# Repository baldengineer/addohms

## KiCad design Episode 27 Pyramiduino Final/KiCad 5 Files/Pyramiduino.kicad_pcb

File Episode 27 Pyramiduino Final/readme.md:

For more information on this video, visit https://addohms.squarespace.com/diy-arduino-turn-on.

The "Arduino Code" directory has the "exercise.ino" showed near the end.
"KiCad 5 Files" include the final schematic and PCB files for the series

-James
The Bald Engineer

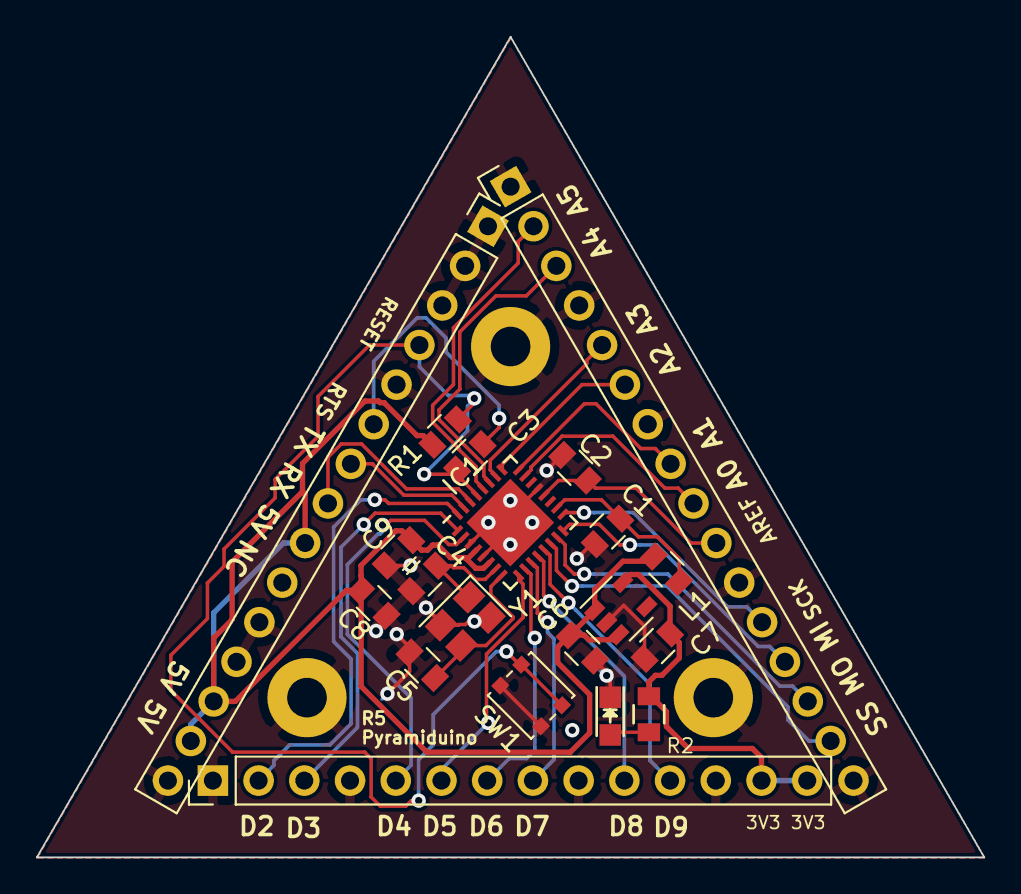
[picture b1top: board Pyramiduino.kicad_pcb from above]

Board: 2 copper layers, 52.6 x 45.6 mm, 23 parts (0 on the bottom side), 30 nets.

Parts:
C1, C3, C9: 100nF; C_0805
C2: 10nF; C_0805
C4, C5: 22pF; C_0805
C6, C7, C8: 1uF; C_0805
D1: LED; LED_0805
IC1: ATMEGA328-A; QFN-32-1EP_5x5mm_Pitch0.5mm-GND
L1: 10uH; C_0805
P1: CONN_01X16; Pin_Header_Straight_1x16_Pitch2.54mm
P2: CONN_01X14; Pin_Header_Straight_1x15_Pitch2.54mm
P3: CONN_01X14; Pin_Header_Straight_1x14_Pitch2.54mm
P4, P5, P6: CONN_01X01; MountingHole_2.2mm_M2_Pad
R1: 100K; C_0805
R2: 1k; C_0805
SW1: SW_PUSH; SW_SPST_PTS830
U1: 3v3; SOT-23-5
Y1: 16M; FA238-4pin_3.2x2.5mm_Offset

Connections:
+3V3: C7.2, P3.13, P3.14, R2.1, U1.5
/328-RX: IC1.30, P2.8
/328-TX: IC1.31, P2.7
/A0: IC1.23, P1.9
/A1: IC1.24, P1.8
/A2: IC1.25, P1.6
/A3: IC1.26, P1.5
/A4: IC1.27, P1.3
/A5: IC1.28, P1.2
/AREF: C2.1, IC1.20, P1.10
/D2: IC1.32, P3.2
/D3: IC1.1, P3.3
/D4: IC1.2, P3.5
/D5: IC1.9, P3.6
/D6: IC1.10, P3.7
/D7: IC1.11, P3.8
/D8: IC1.12, P3.10
/D9: IC1.13, P3.11
/MISO: IC1.16, P1.13
/MOSI: IC1.15, P1.14
/RESET: C3.1, IC1.29, P2.4, R1.2, SW1.2
/RTS: C3.2, P2.6
/SCK: IC1.17, P1.12
/SS: IC1.14, P1.15
/X_N: C5.2, IC1.8, Y1.3
/X_P: C4.2, IC1.7, Y1.1
GND: C1.2, C2.2, C4.1, C5.1, C6.1, C7.1, C8.2, C9.2, D1.1, IC1.3, IC1.5, IC1.21, P1.1, P1.4, P1.7, P1.11, P1.16, P2.1, P2.2, P2.3, P2.5, P2.11, P2.12, P2.15, P3.1, P3.4, P3.9, P3.12, P4.1, P5.1, P6.1, SW1.1, U1.2, Y1.2, Y1.4
unnamed: C1.1, IC1.18, L1.1
unnamed: D1.2, R2.2
VCC: C6.2, C8.1, C9.1, IC1.4, IC1.6, L1.2, P2.9, P2.13, P2.14, R1.1, U1.1, U1.3

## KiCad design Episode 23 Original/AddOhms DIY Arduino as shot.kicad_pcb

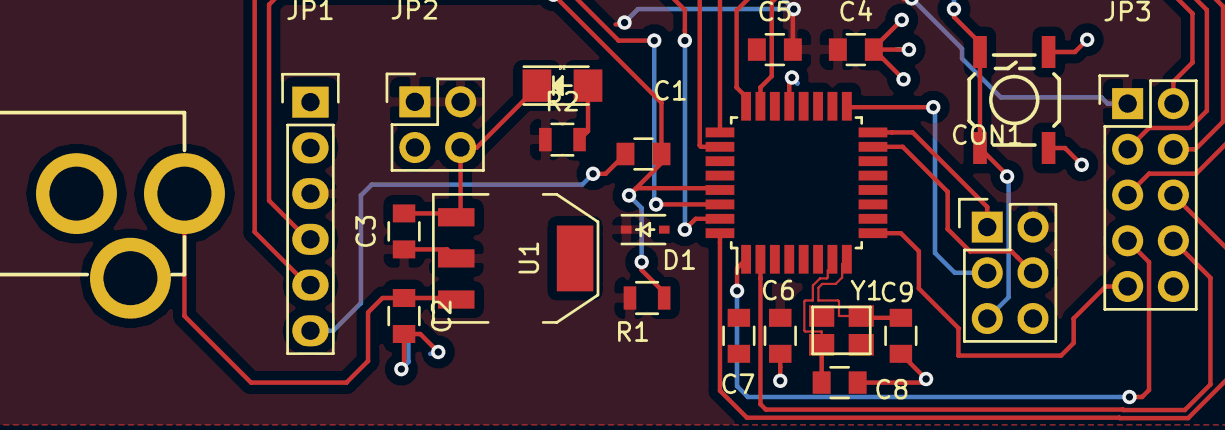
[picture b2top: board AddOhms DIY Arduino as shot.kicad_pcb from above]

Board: 2 copper layers, 22 parts (0 on the bottom side), 21 nets.

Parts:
C1, C4, C5, C6, C7: 100nF; C_0805
C2: 10uF; C_0805
C3: 1uF; C_0805
C8, C9: 22pF; C_0805
CON1: AVR-ISP-6; Pin_Header_Straight_2x03
D1: D; SOD-323
D2: PWR; LED-1206
J1: VIN; POWER_JACK_PTH
JP1: M06; Pin_Header_Straight_1x06
JP2: 5V_HDR; Pin_Header_Straight_2x02
JP3: M10; Pin_Header_Straight_2x05
R1: R; R_0805
R2: 1K; R_0805
SW1: RESET; SW_PUSHBUTTON_SMD
U1: NCP1117-12_TO252; SOT-223
U2: ATMEGA168A-AU; TQFP-32_7x7mm_Pitch0.8mm
Y1: Crystal; crystal_FA238-TSX3225

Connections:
+5V: C3.1, C4.1, C5.1, C6.1, C7.1, CON1.2, D1.1, JP1.3, JP2.1, JP2.2, JP3.1, R1.1, R2.1, U1.2, U2.4, U2.6, U2.18, U2.20
/328_RX: JP1.4, U2.30
/328_TX: JP1.5, U2.31
/A0: JP3.2, U2.23
/A1: JP3.3, U2.24
/A2: JP3.4, U2.25
/A3: JP3.5, U2.26
/D2: JP3.6, U2.32
/D3: JP3.7, U2.1
/D4: JP3.8, U2.2
/D5: JP3.9, U2.9
/MISO: CON1.1, U2.16
/MOSI: CON1.4, U2.15
/RESET: C1.1, CON1.5, R1.2, SW1.1, U2.29
/RTS: C1.2, JP1.6
/SCK: CON1.3, U2.17
/VIN: C2.1, J1.1, U1.3
/X_N: C9.2, U2.8, Y1.2
/X_P: C8.2, U2.7, Y1.1
GND: C2.2, C3.2, C4.2, C5.2, C6.2, C7.2, C8.1, C9.1, CON1.6, D1.2, D2.1, J1.2, J1.3, JP1.1, JP2.3, JP2.4, JP3.10, SW1.2, U1.1, U2.3, U2.5, U2.21
unnamed: D2.2, R2.2

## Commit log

2018-01-17 Create readme.md
    Initial Commit
2018-01-17 Add files via upload
    DIY Arduino Schematic (As Shot)
2018-02-26 Corrected Episode 23
    Works for KiCad 4.07 now.
2018-02-26 Pyramiduino Initial Commit
    AddOhms Episode #24 shows how to take a DIY Arduino schematic and create a trianglular PCB in KiCad.
2018-07-06 Rev5 Updates
